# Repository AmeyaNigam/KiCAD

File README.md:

# KiCAD
A collection of 50 PCB design projects using KiCad, ranging from basic power supplies to advanced microcontrollers.

# 50 Projects in KiCad

## Project 1: Fixed 5V Power Supply
A simple DC-DC regulator circuit that converts 7V-12V input into a stable 5V output.

### Features:
* **L7805** Linear Regulator
* **GND Plane** for heat dissipation and signal stability
* **LED Indicator** for power status

## Project 2: Automatic Night Light
An automatic night light circuit that detects ambient light using an LDR and drives an LED using a BJT transistor switch.

### Features:
* **LDR + Potentiometer** voltage divider for sensitivity control
* **2N3904 NPN BJT** transistor switch
* **LED Indicator** for output

## Project 3: 555 Timer LED Flasher
An astable multivibrator circuit built around an NE555 timer IC that continuously flashes an LED at a set frequency.

* **NE555 Timer IC** configured in astable mode for continuous square-wave oscillation
* **Adjustable Timing Network** using resistors and capacitor 
* **Power Supply Decoupling** and control voltage filtering for stable operation
* **LED Indicator Stage** driven by current-limiting resistor

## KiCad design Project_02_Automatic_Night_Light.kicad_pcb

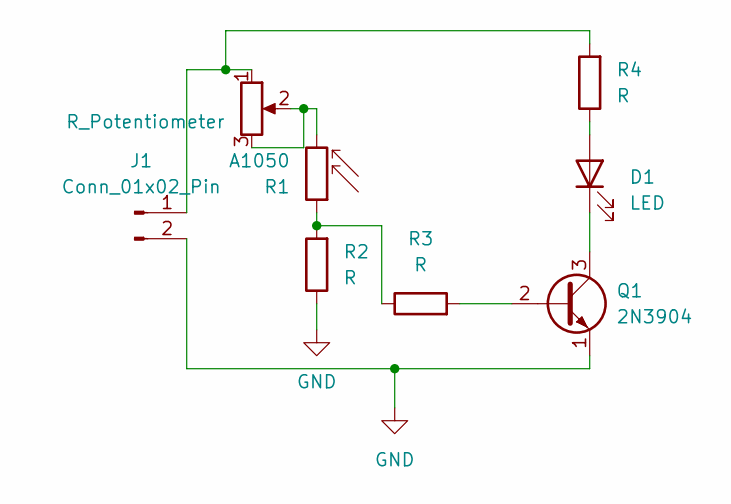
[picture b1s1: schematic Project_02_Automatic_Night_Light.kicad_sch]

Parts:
D1: LED; LED_D5.0mm
J1: Conn_01x02_Pin; PinSocket_1x02_P2.54mm_Vertical
Q1: 2N3904; TO-92_Inline
R1: A1050; R_Axial_DIN0207_L6.3mm_D2.5mm_P7.62mm_Horizontal
R2, R3, R4: R; R_Axial_DIN0207_L6.3mm_D2.5mm_P7.62mm_Horizontal
RV1: R_Potentiometer; Potentiometer_Bourns_3296W_Vertical

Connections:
GND: J1.2, Q1.1 (E), R2.1
unnamed: D1.2 (A), R4.1
unnamed: D1.1 (K), Q1.3 (C)
unnamed: J1.1, R4.2, RV1.1
unnamed: Q1.2 (B), R3.2
unnamed: R1.1, R2.2, R3.1
unnamed: R1.2, RV1.2, RV1.3

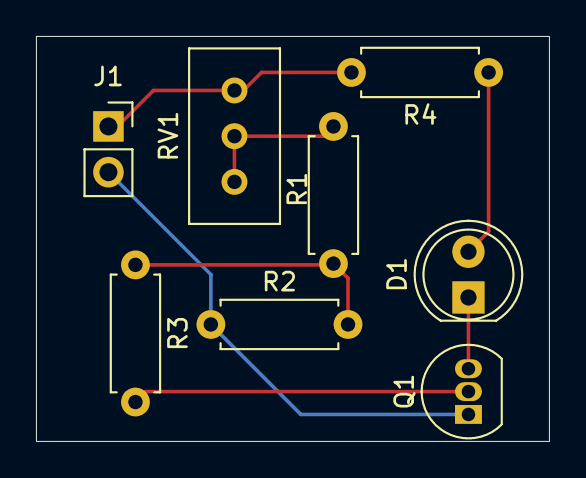
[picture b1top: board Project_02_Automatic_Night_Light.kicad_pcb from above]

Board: 2 copper layers, 28.5 x 22.5 mm, 8 parts (0 on the bottom side), 7 nets.

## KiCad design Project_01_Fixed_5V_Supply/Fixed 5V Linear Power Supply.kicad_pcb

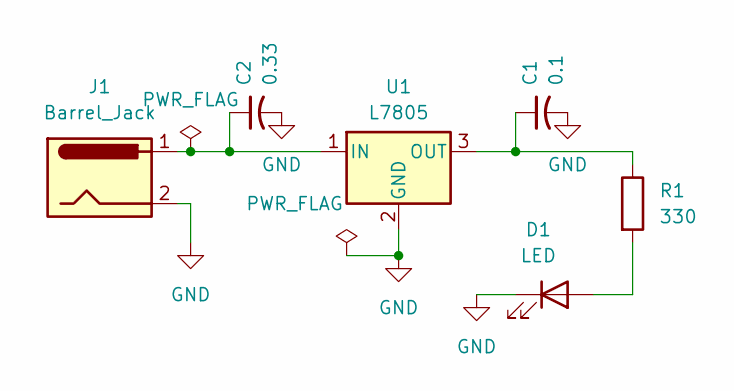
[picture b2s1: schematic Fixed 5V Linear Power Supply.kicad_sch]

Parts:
C1: 0.1; CP_Radial_D5.0mm_P2.50mm
C2: 0.33; CP_Radial_D5.0mm_P2.50mm
D1: LED; LED_D5.0mm
J1: Barrel_Jack; BarrelJack_CUI_PJ-063AH_Horizontal
R1: 330; R_Axial_DIN0207_L6.3mm_D2.5mm_P7.62mm_Horizontal
U1: L7805; TO-220-3_Vertical

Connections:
GND: C1.2, C2.2, D1.1 (K), J1.2, U1.2 (GND)
unnamed: D1.2 (A), R1.2
unnamed: C2.1, J1.1, U1.1 (IN)
unnamed: C1.1, R1.1, U1.3 (OUT)

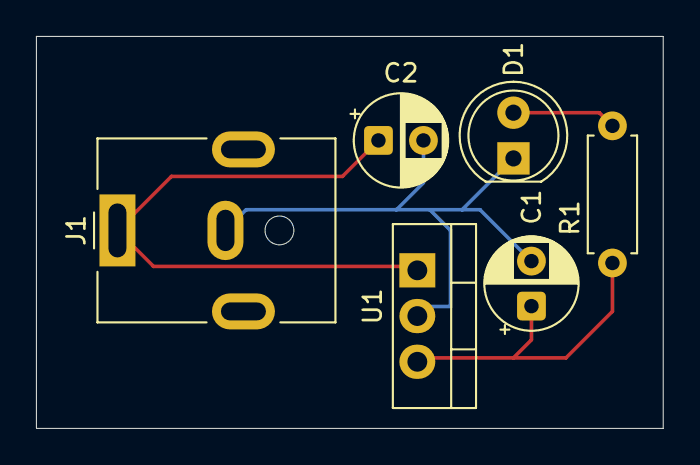
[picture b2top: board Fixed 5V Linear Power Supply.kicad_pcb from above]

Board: 2 copper layers, 34.8 x 21.8 mm, 6 parts (0 on the bottom side), 4 nets.

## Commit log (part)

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2026-04-27 Create Fixed 5V Linear Power Supply
2026-04-27 Create keep
